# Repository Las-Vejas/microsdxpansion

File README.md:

# microsdxpansion
An expansion module for Hackxpansion that contains a micro sd slot.

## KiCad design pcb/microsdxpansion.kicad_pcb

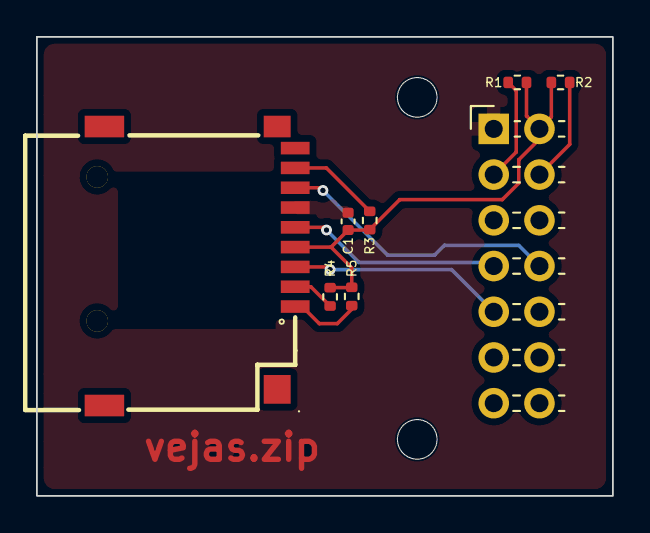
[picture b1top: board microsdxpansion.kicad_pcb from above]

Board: 2 copper layers, 32.0 x 25.5 mm, 8 parts (0 on the bottom side), 10 nets.

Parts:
C1: 100nf; C_0402_1005Metric
J1: Male_Module
J2: Micro_SD_Card; TF-SMD_TF-PUSH
R1: 1k; R_0402_1005Metric
R2: 91k; R_0402_1005Metric
R3, R4, R5: 10k; R_0402_1005Metric

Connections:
+3V3: C1.1, J1.2 (3V3), J2.4 (VDD), R1.1, R2.1, R3.1, R4.1, R5.1
/MISO: J1.8 (SPI_MISO), J2.7 (DAT0)
/MOSI: J1.9 (SPI_MOSI), J2.3 (CMD)
/SCK: J1.7 (SPI_SCK), J2.5 (CLK)
GND: C1.2, J1.1 (GND), J2.6 (VSS)
unnamed: J1.3 (MD0), R1.2
unnamed: J1.4 (MD1), R2.2
unnamed: J2.8 (DAT1), R3.2
unnamed: J2.1 (DAT2), R5.2
unnamed: J2.2 (DAT3/CD), R4.2

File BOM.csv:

Reference,Qty,Price,Value,LCSC Part #
C1,1,0.50 $US,100nf,C60474
R1,1,0.15 $US,1k,C140197
R2,1,0.17 $US,91k,C2909393
"R3,R4,R5",3,0.16 $US,10k,C2906861
J2,1,0.63 $US,Micro_SD_Card,C393941
PCB,5,4.00 $US,N/A,N/A
TOTAL,,5.61 $US,,
